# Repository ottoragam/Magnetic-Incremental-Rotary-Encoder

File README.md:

# Magnetic-Incremental-Rotary-Encoder

----------------------------------------------------------------------
Magnetic Incremental Rotary Encoder (c) by Gino Magarotto

Magnetic Incremental Rotary Encoder is licensed under a
Creative Commons Attribution-ShareAlike 3.0 Unported License.

You should have received a copy of the license along with this
work.  If not, see <http://creativecommons.org/licenses/by-sa/3.0/>.

----------------------------------------------------------------------

This project aims to provide a compact, easy to use, relatively high resolution and arguably cheap encoder. It uses the AS5040 magnetic rotary encoder IC from Austria Microsystems.

Project log on https://hackaday.io/project/8418-magnetic-incremental-rotary-encoder

Included are.stl and .step files for the case, and .sch and .brd for the PCB.

The PCB is double sided and measures 20 x 20 mm. It could be home etched or manufactured using some low cost prototyping service. The case is designed to be milled, 3D printed or laser cut (the top part). A 3 mm or 1/8 in tap is also needed for threading two holes on the case cover.

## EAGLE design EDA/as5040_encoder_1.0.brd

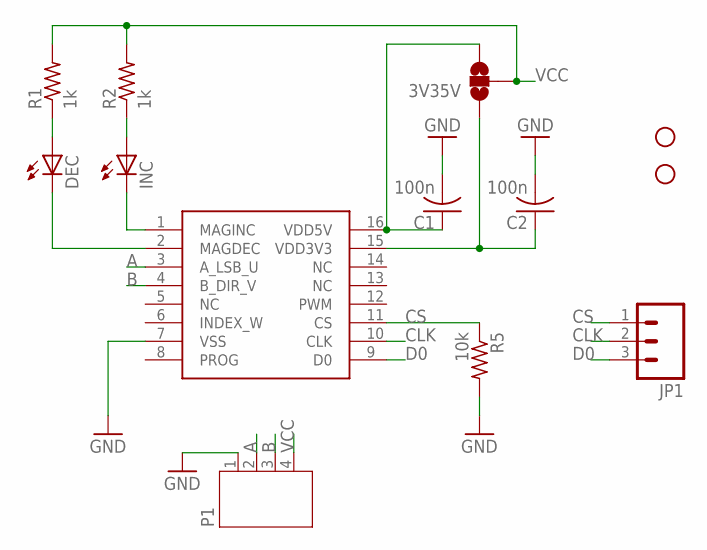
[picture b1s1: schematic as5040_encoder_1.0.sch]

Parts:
3V35V: SOLDERJUMPER_2WAYPASTE1&2&3; SJ_3_PASTE1&2&3
5040: AS5040; SSOP16
C1, C2: 100n; C0603K
DEC: LEDCHIPLED_0603; CHIPLED_0603
INC: LEDCHIPLED_0603; CHIPLED_0603
JP1: M03PTH; 1X03
P1: JST-PH4
R1, R2: 1k; R0603
R5: 10k; R0603
STANDOFF1, STANDOFF2: STAND-OFF

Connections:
A: 5040.3 (A_LSB_U), P1.2
B: 5040.4 (B_DIR_V), P1.3
CLK: 5040.10 (CLK), JP1.2
CS: 5040.11 (CS), JP1.1, R5.1
D0: 5040.9 (D0), JP1.3
GND: 5040.7 (VSS), C1.2, C2.2, P1.1, R5.2
unnamed: INC.A, R2.1
unnamed: DEC.A, R1.1
unnamed: 5040.1 (MAGINC), INC.C
unnamed: 5040.2 (MAGDEC), DEC.C
unnamed: 3V35V.3, 5040.16 (VDD5V), C1.1
unnamed: 3V35V.1, 5040.15 (VDD3V3), C2.1
VCC: 3V35V.2, P1.4, R1.2, R2.2

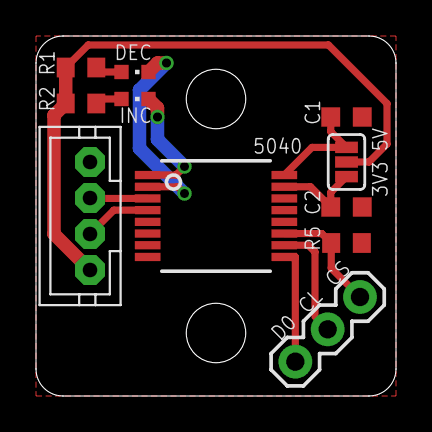
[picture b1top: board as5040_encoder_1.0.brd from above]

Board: 2 copper layers, 20.0 x 20.0 mm, 13 parts (0 on the bottom side), 13 nets.

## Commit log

2015-11-13 :tada: Added .gitattributes
2015-11-13 EDA Files
    Eagle design iles or the PCB and gerbers
2015-11-13 Datasheet
2015-11-13 EDA Files
2015-11-13 Revert "EDA Files"
    This reverts commit 6de166a53c72d63280062df4a804821b19d4f5fb.
2015-11-13 Datasheets, Drawings, BOM
2015-11-20 CAD designs
2015-11-20 Pics
2015-11-20 Added BOM
2016-02-09 add more pics

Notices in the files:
parts and their libraries:
SparkFun-Retired: Licensing:Creative Commons ShareAlike 4.0 International - https://creativecommons.org/licenses/by-sa/4.0
